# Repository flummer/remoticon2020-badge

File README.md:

# Hackaday Remoticon 2020 Unofficial Badge by Thomas Flummer

## Physical badges for virtual events

This is an experiment and you are part of it. There is [no official badge](https://twitter.com/SophiKravitz/status/1308486813963767809) but I have been trying out the nightly builds of KiCad lately and there is a lot of awesome new features, that you can try too.

This badge is meant to be a basis for whatever you think would be cool on a badge. Simply fork this repository, change it to you liking and you can order exactly the badge you think would be cool, just remember to share it.

There is about a month until the 2020 Remoticon so there should be enough time to have the badge in hand for the event, though you might need to get some fast shipping on those PCBs.

## Mostly prototyping area and decoration

This badge is partly inspired by the event graphics and partly by the [first Superconference badge by Chris Gammell](https://twitter.com/Chris_Gammell/status/666028712828125184) and it's in the hope to see some fancy hacking, some free form soldering of tiny components or maybe the use this badge as base for a circuit sculpture of some sort. There are plenty of exposed copper pads to solder on and since more and more move in the direction of surface mount parts, there are a lot of area for those.

## SMD Soldering challenge

Another stable of many hacker events and not least the ones around the Hackaday crowd are soldering challenges with tiny little parts, competing not only on speed, but also on functionality and how nice the solderjoints are, component position, etc.

So in an attempt at bringing a little bit if the Superconference feel into the real world for this virtual event, I have added the [SMD challenge circuit](https://github.com/aspro648/KiCad/tree/master/projects/Attiny/Attiny85ChallengeHackaday2020) by [MakersBox](https://www.tindie.com/stores/makersbox/) as a way to show your awesome hand soldering capabilities.

## Adafruit Feather mounting option

On the back, I have added a few footprints for some SDM double row headers and broken all pins out to some test points. This is so that you don't have to solder wires or similar directly to the Feather, in case you want to reuse it for another project. I think the Feather platform is a great solution for badge prototypes, since they all have onboard LiPo power and charge funtionality, making it really easy to get a wearable design operational.

The GND on the Feather and GND on the SMD soldering challenge is connected and if you want to power the soldering challenge from the Feather, you can add a blob of solder on the small jumper on the back and then skip the coin cell all together.

## Making your own

If you want to make your own, I have included the gerbers, in case you don't want to install the nightly version of KiCad.

There is also a [shared projects at OSHPark](https://oshpark.com/shared_projects/1NAp0lZJ), just remember to select AfterDark, when checking out to get the same look as on the render in the top of this page. It will also function in Purple (or any other color for that matter), but will have a slightly different look.

The parts needed for the SMD Soldering challenge are listed on [MakersBox repository](https://github.com/aspro648/KiCad/tree/master/projects/Attiny/Attiny85ChallengeHackaday2020) and exactly which header you use for mounting a feather depens a little on what you have mounted on the Feather. It's a simple double row SMD footprint and the male pin breakaway type is probably the cheapest, and a low profile version is best, to keep the overall thickness as low as possible.

## Please share

If you decide to make this badge or a variant of it, please share images so we can all see it and get inspired. If sharing on social media, please use the #badgelife tag and please let [me](https://thomasflummer.com/) know, I would love to see what you have made!

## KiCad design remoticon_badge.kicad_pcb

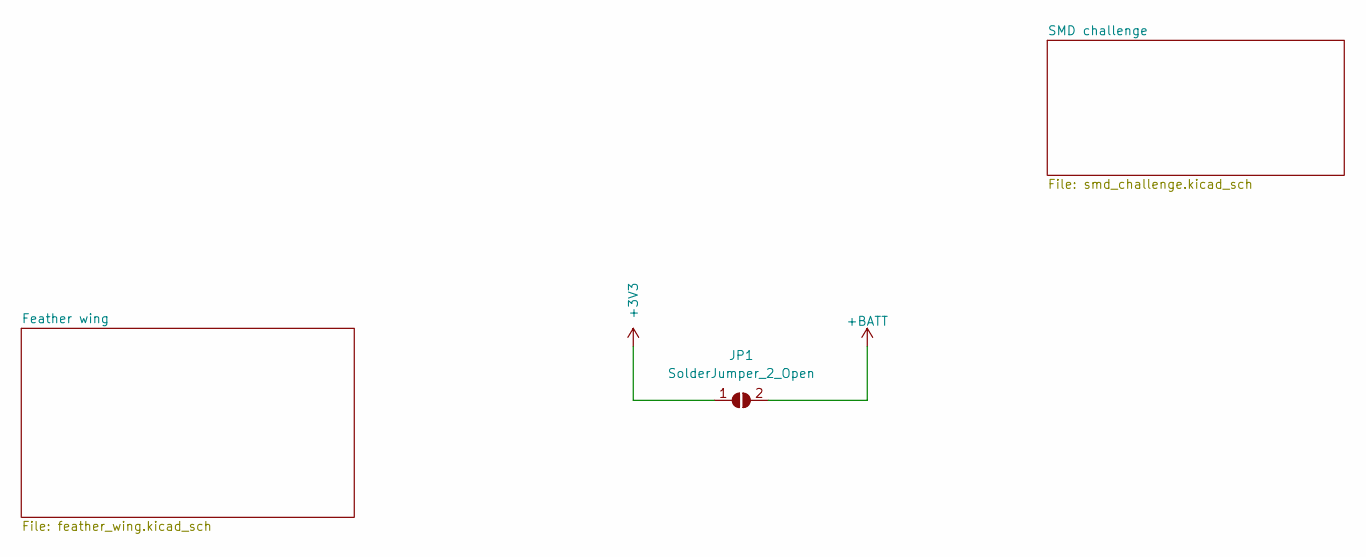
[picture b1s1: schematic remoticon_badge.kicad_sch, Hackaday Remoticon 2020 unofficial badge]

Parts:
JP1: SolderJumper_2_Open; SolderJumper-2_P1.3mm_Open_TrianglePad1.0x1.5mm

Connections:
+3V3: JP1.1 (A); also elsewhere on the board
+BATT: JP1.2 (B); also elsewhere on the board

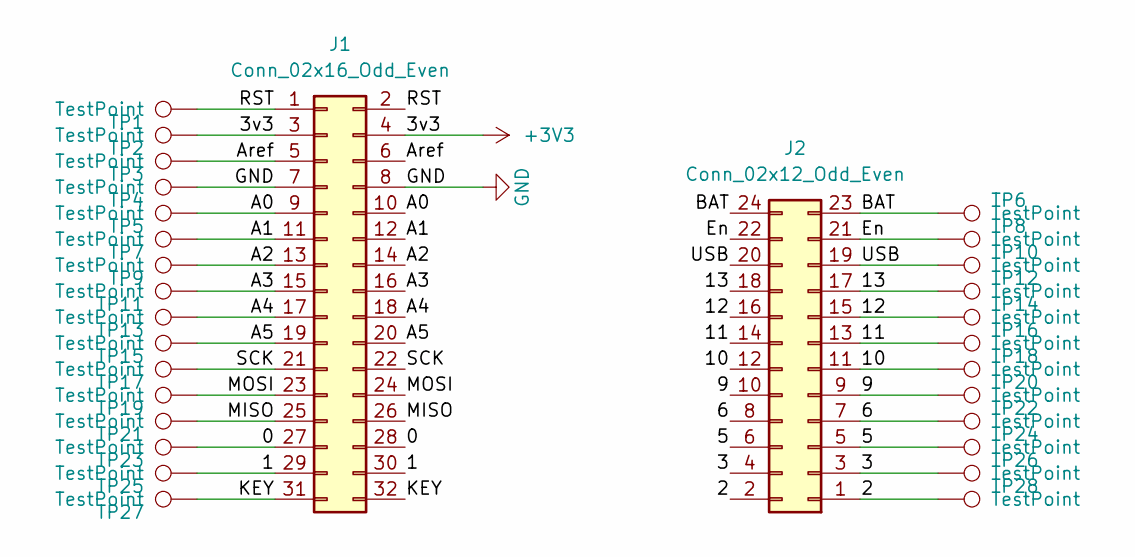
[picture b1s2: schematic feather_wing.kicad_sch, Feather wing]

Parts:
J1: Conn_02x16_Odd_Even; PinHeader_2x16_P2.54mm_Vertical_SMD
J2: Conn_02x12_Odd_Even; PinHeader_2x12_P2.54mm_Vertical_SMD
TP1, TP2, TP3, TP4, TP5, TP6, TP7, TP8, TP9, TP10, TP11, TP12, TP13, TP14, TP15, TP16, TP17, TP18, TP19, TP20, TP21, TP22, TP23, TP24, TP25, TP26, TP27, TP28: TestPoint; TestPoint_Pad_D1.5mm

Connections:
+3V3: J1.3, J1.4, TP2.1; also elsewhere on the board
/Feather wing/0: J1.27, J1.28, TP23.1
/Feather wing/1: J1.29, J1.30, TP25.1
/Feather wing/2: J2.1, J2.2, TP28.1
/Feather wing/3: J2.3, J2.4, TP26.1
/Feather wing/5: J2.5, J2.6, TP24.1
/Feather wing/6: J2.7, J2.8, TP22.1
/Feather wing/9: J2.9, J2.10, TP20.1
/Feather wing/10: J2.11, J2.12, TP18.1
/Feather wing/11: J2.13, J2.14, TP16.1
/Feather wing/12: J2.15, J2.16, TP14.1
/Feather wing/13: J2.17, J2.18, TP12.1
/Feather wing/A0: J1.9, J1.10, TP5.1
/Feather wing/A1: J1.11, J1.12, TP7.1
/Feather wing/A2: J1.13, J1.14, TP9.1
/Feather wing/A3: J1.15, J1.16, TP11.1
/Feather wing/A4: J1.17, J1.18, TP13.1
/Feather wing/A5: J1.19, J1.20, TP15.1
/Feather wing/Aref: J1.5, J1.6, TP3.1
/Feather wing/BAT: J2.23, J2.24, TP6.1
/Feather wing/En: J2.21, J2.22, TP8.1
/Feather wing/KEY: J1.31, J1.32, TP27.1
/Feather wing/MISO: J1.25, J1.26, TP21.1
/Feather wing/MOSI: J1.23, J1.24, TP19.1
/Feather wing/RST: J1.1, J1.2, TP1.1
/Feather wing/SCK: J1.21, J1.22, TP17.1
/Feather wing/USB: J2.19, J2.20, TP10.1
GND: J1.7, J1.8, TP4.1; also elsewhere on the board

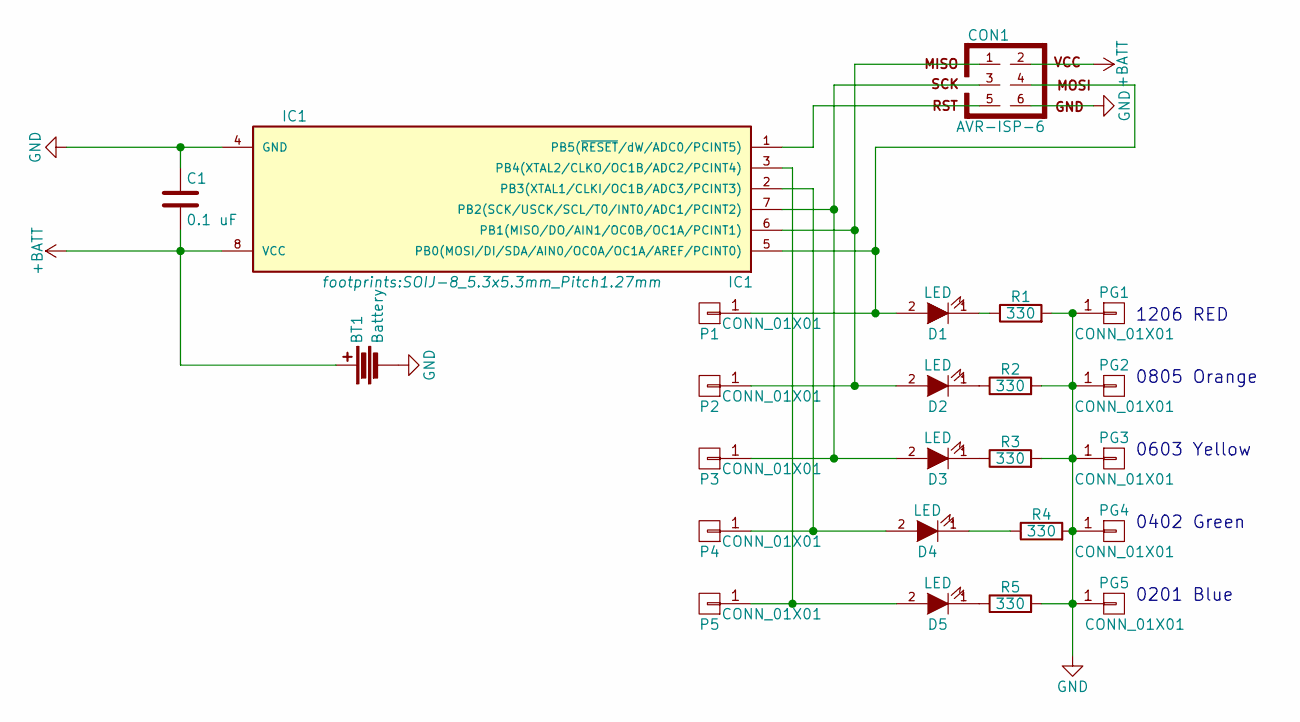
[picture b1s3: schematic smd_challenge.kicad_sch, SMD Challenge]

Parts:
BT1: Battery; BATT_CR2032_SMD
C1: 0.1 uF; C_1206_HandSoldering
CON1: AVR-ISP-6
D1: LED; LED-1206
D2: LED; LED-0805
D3: LED; LED-0603
D4: LED; LED_0402
D5: LED; LED_0201
IC1: IC1; SOIJ-8_5.3x5.3mm_Pitch1.27mm
P1, P2, P3, P4, P5: CONN_01X01; testPad
PG1, PG2, PG3, PG4, PG5: CONN_01X01; testPad
R1: 330; R_1206
R2: 330; R_0805
R3: 330; R_0603
R4: 330; R_0402
R5: 330; R_0201

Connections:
+BATT: BT1.1, C1.2, CON1.2, IC1.8 (VCC); also elsewhere on the board
GND: BT1.2, C1.1, CON1.6, IC1.4 (GND), PG1.1, PG2.1, PG3.1, PG4.1, PG5.1, R1.2, R2.2, R3.2, R4.2, R5.2; also elsewhere on the board
unnamed: CON1.1, D2.2 (A), IC1.6 (PB1(MISO/DO/AIN1/OC0B/OC1A/PCINT1)), P2.1
unnamed: CON1.3, D3.2 (A), IC1.7 (PB2(SCK/USCK/SCL/T0/INT0/ADC1/PCINT2)), P3.1
unnamed: CON1.4, D1.2 (A), IC1.5 (PB0(MOSI/DI/SDA/AIN0/OC0A/OC1A/AREF/PCI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), P1.1
unnamed: CON1.5, IC1.1 (PB5(~RESET~/dW/ADC0/PCINT5))
unnamed: D1.1 (K), R1.1
unnamed: D2.1 (K), R2.1
unnamed: D3.1 (K), R3.1
unnamed: D4.1 (K), R4.1
unnamed: D4.2 (A), IC1.2 (PB3(XTAL1/CLKI/OC1B/ADC3/PCINT3)), P4.1
unnamed: D5.1 (K), R5.1
unnamed: D5.2 (A), IC1.3 (PB4(XTAL2/CLKO/OC1B/ADC2/PCINT4)), P5.1

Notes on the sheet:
1206 RED
0805 Orange
0603 Yellow
0402 Green
0201 Blue

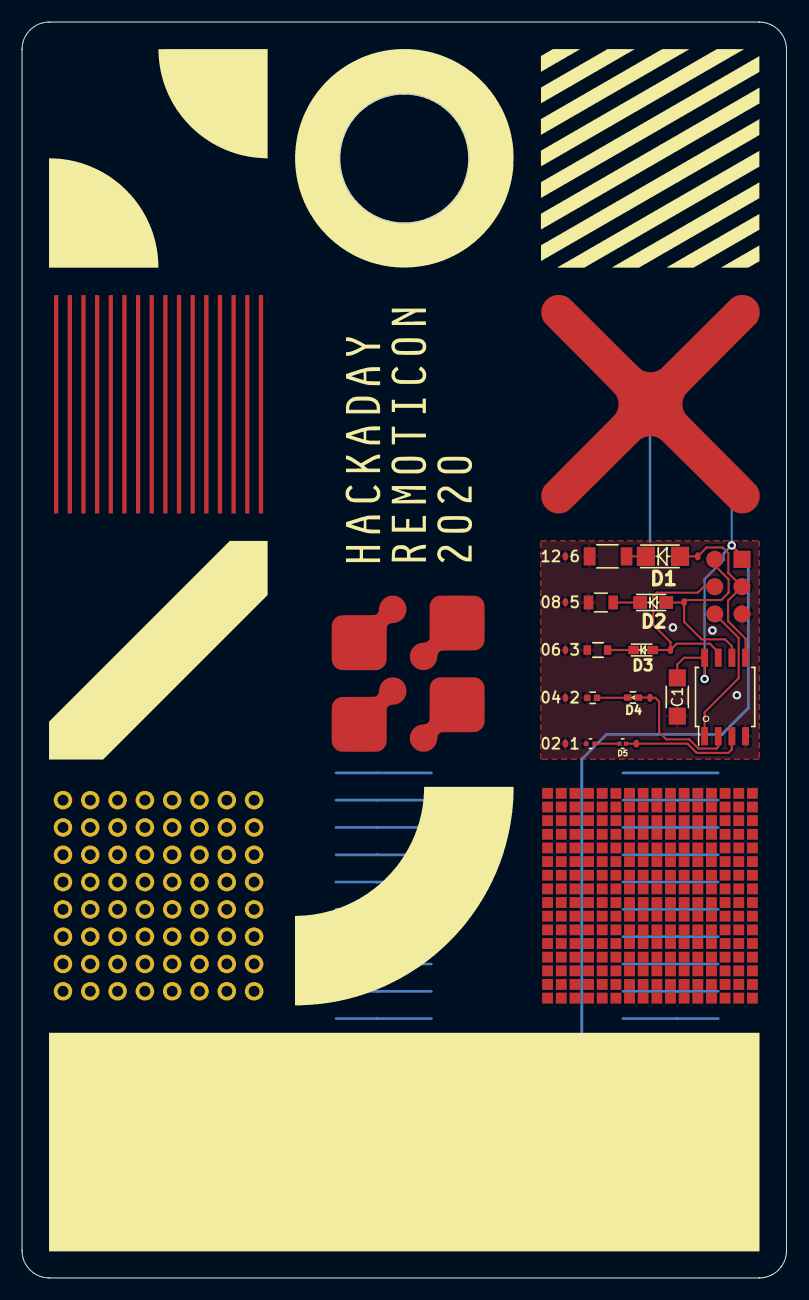
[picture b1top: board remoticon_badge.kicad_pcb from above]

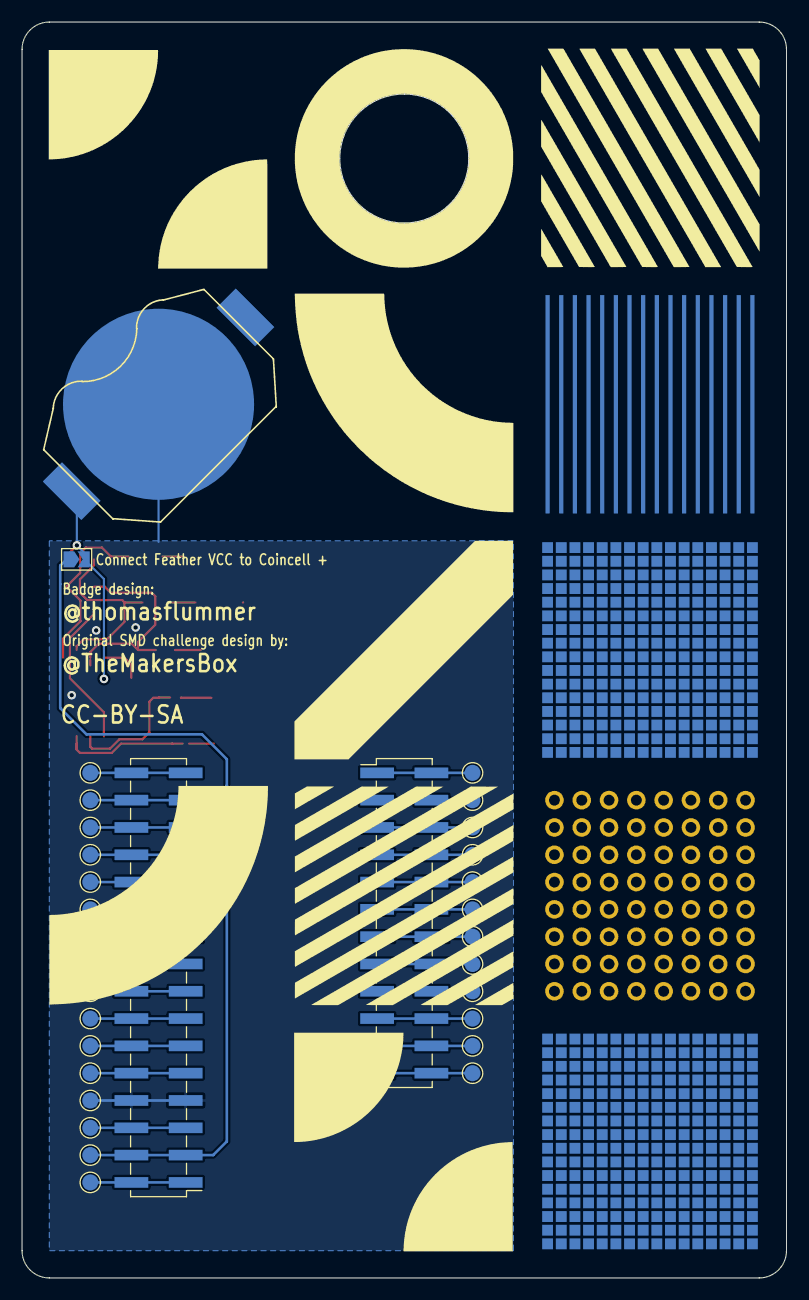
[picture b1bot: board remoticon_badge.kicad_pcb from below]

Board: 2 copper layers, 71.1 x 116.8 mm, 55 parts (32 on the bottom side), 40 nets.

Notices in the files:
feather_wing.kicad_sch:
CC-BY-SA
